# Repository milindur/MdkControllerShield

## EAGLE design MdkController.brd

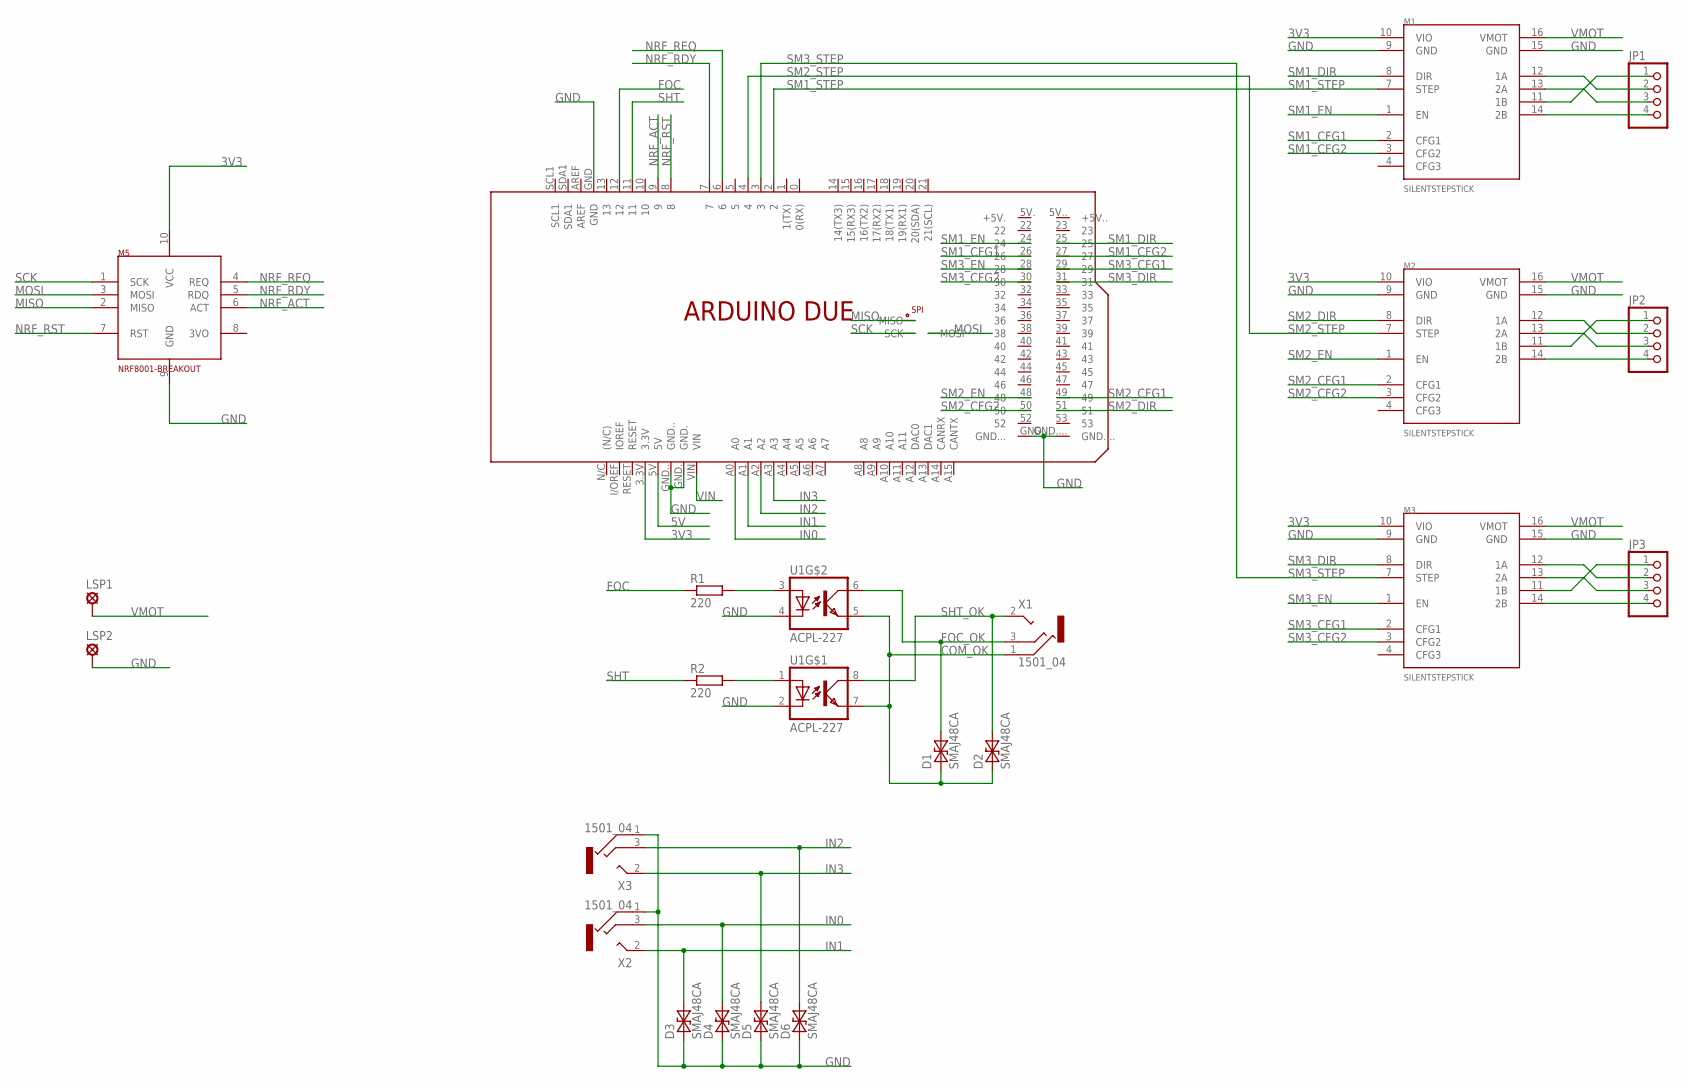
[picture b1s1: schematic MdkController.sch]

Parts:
D1, D2, D3, D4, D5, D6: SMAJ48CA; DO214AC
JP1, JP2, JP3: PINHD-1X4; 1X04
LSP1, LSP2: SE14
M1, M2, M3: SILENTSTEPSTICK
M5: NRF8001-BREAKOUT
R1, R2: 220; R0805
U1: ACPL-227; SO8
U$1: ARDUINO_DUE_PINS_ONLY
X1, X2, X3: 1501_04; 1501_05

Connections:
3V3: M1.10 (VIO), M2.10 (VIO), M3.10 (VIO), M5.10 (VCC), U$1.3.3V
5V: U$1.5V
COM_OK: D1.1, D2.1, U1.5 (EMIT), U1.7 (EMIT), X1.1
FOC: R1.1, U$1.12
FOC_OK: D1.2, U1.6 (COL), X1.3
GND: D3.1, D4.1, D5.1, D6.1, LSP2.MP, M1.9 (GND), M1.15 (GND), M2.9 (GND), M2.15 (GND), M3.9 (GND), M3.15 (GND), M5.9 (GND), U1.2 (C), U1.4 (C), U$1.GND, U$1.GND., U$1.GND.., U$1.GND..., U$1.GND...., X2.1, X3.1
IN0: D4.2, U$1.A0, X2.3
IN1: D3.2, U$1.A1, X2.2
IN2: D6.2, U$1.A2, X3.3
IN3: D5.2, U$1.A3, X3.2
MISO: M5.2 (MISO), U$1.MISO
MOSI: M5.3 (MOSI), U$1.MOSI
unnamed: R1.2, U1.3 (A)
unnamed: R2.2, U1.1 (A)
unnamed: JP1.1, M1.11 (1B)
unnamed: JP1.2, M1.12 (1A)
unnamed: JP1.3, M1.13 (2A)
unnamed: JP1.4, M1.14 (2B)
unnamed: JP2.1, M2.11 (1B)
unnamed: JP2.2, M2.12 (1A)
unnamed: JP2.3, M2.13 (2A)
unnamed: JP2.4, M2.14 (2B)
unnamed: JP3.1, M3.11 (1B)
unnamed: JP3.2, M3.12 (1A)
unnamed: JP3.3, M3.13 (2A)
unnamed: JP3.4, M3.14 (2B)
NRF_ACT: M5.6 (ACT), U$1.9
NRF_RDY: M5.5 (RDQ), U$1.7
NRF_REQ: M5.4 (REQ), U$1.6
NRF_RST: M5.7 (RST), U$1.8
SCK: M5.1 (SCK), U$1.SCK
SHT: R2.1, U$1.11
SHT_OK: D2.2, U1.8 (COL), X1.2
SM1_CFG1: M1.2 (CFG1), U$1.26
SM1_CFG2: M1.3 (CFG2), U$1.27
SM1_DIR: M1.8 (DIR), U$1.25
SM1_EN: M1.1 (EN), U$1.24
SM1_STEP: M1.7 (STEP), U$1.2
SM2_CFG1: M2.2 (CFG1), U$1.49
SM2_CFG2: M2.3 (CFG2), U$1.50
SM2_DIR: M2.8 (DIR), U$1.51
SM2_EN: M2.1 (EN), U$1.48
SM2_STEP: M2.7 (STEP), U$1.4
SM3_CFG1: M3.2 (CFG1), U$1.29
SM3_CFG2: M3.3 (CFG2), U$1.30
SM3_DIR: M3.8 (DIR), U$1.31
SM3_EN: M3.1 (EN), U$1.28
SM3_STEP: M3.7 (STEP), U$1.3
VIN: U$1.VIN
VMOT: LSP1.MP, M1.16 (VMOT), M2.16 (VMOT), M3.16 (VMOT)

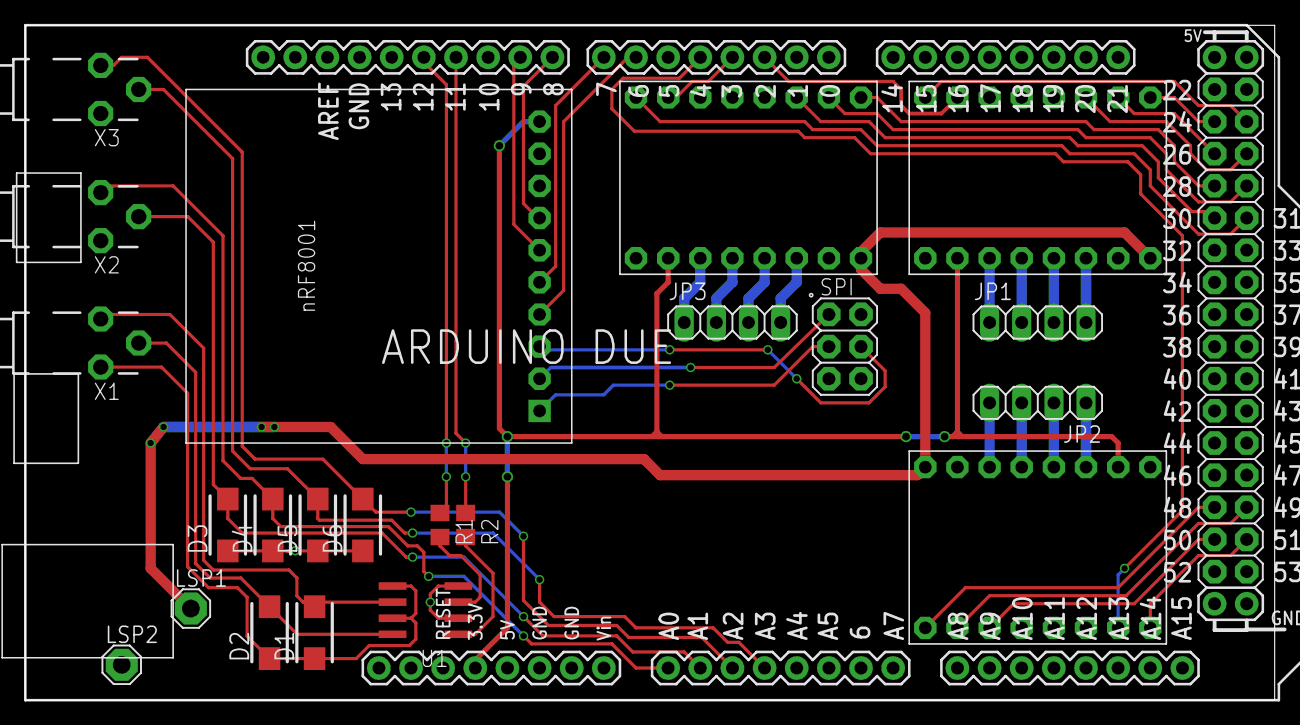
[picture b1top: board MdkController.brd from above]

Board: 2 copper layers, 98.7 x 53.3 mm, 22 parts (0 on the bottom side), 48 nets.

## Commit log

2015-11-07 Revision v1
2015-11-17 Überarbeitung (4. Stepper entfernt, etwas aufgeräumt)
